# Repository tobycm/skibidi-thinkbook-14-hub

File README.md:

# skibidi thinkbook 14 hub

a very skibidi usb hub to clip on my laptop.

features:

- usb 3.2 gen 1 hub with gigabit ethernet
- 2 usb-a usb 3.2 gen 1 ports
- 2 usb-c usb 2.0 ports
- 3.5mm audio jack

powered by tusb8042a usb hub controller, rtl8153b gigabit ethernet controller, ch334 usb 2.0 hub controller, and pcm2704 usb dac.

designed in kicad 9

## PCB

## CAD

### Case

### Body

### Top

## BOM

| Item | Quantity | Total Cost | Vendor |
| :--- | :--- | :--- | :--- |
| PCB | 5 | $11.90 | JLCPCB |
| PCBA | 2 | $59.26 | JLCPCB |
| JLCPCB Shipping | 1 | $8.29 | JLCPCB |
| PJ-325C5-G | 5 | $0.90 | LCSC |
| ESD5Z5.0T1G | 20 | $0.67 | LCSC |
| BSMD1206-200-12V | 10 | $0.61 | LCSC |
| BLM21PG221SN1D | 50 | $0.83 | LCSC |
| HR911130C | 3 | $7.68 | LCSC |
| ME6211C33M5G-N | 10 | $0.47 | LCSC |
| 0603WAF4302T5E | 100 | $0.12 | LCSC |
| FRC0603F9531TS | 100 | $0.09 | LCSC |
| 0402WGF2491TCE | 200 | $0.12 | LCSC |
| HC-USB3.0-C26 | 5 | $0.53 | LCSC |
| CYA0650-4.7UH | 5 | $1.28 | LCSC |
| HC-ST-003-01-J | 20 | $2.49 | LCSC |
| TYPE-C 14PLC-H10.0 | 20 | $4.68 | LCSC |
| XL2EL89COI-111YLC-24M | 10 | $0.65 | LCSC |
| XL2EL89COI-111YLC-12M | 10 | $0.67 | LCSC |
| LCSC Shipping | 1 | $16.09 | LCSC |
| Round Hex Cap Screw kit M3 | 1 | $8.52 | Aliexpress |
| Brass Threaded Insert Nut Kit M3 | 1 | $10.54 | Aliexpress |
| **Grand Total** | **-** | **$136.39** | **-** |

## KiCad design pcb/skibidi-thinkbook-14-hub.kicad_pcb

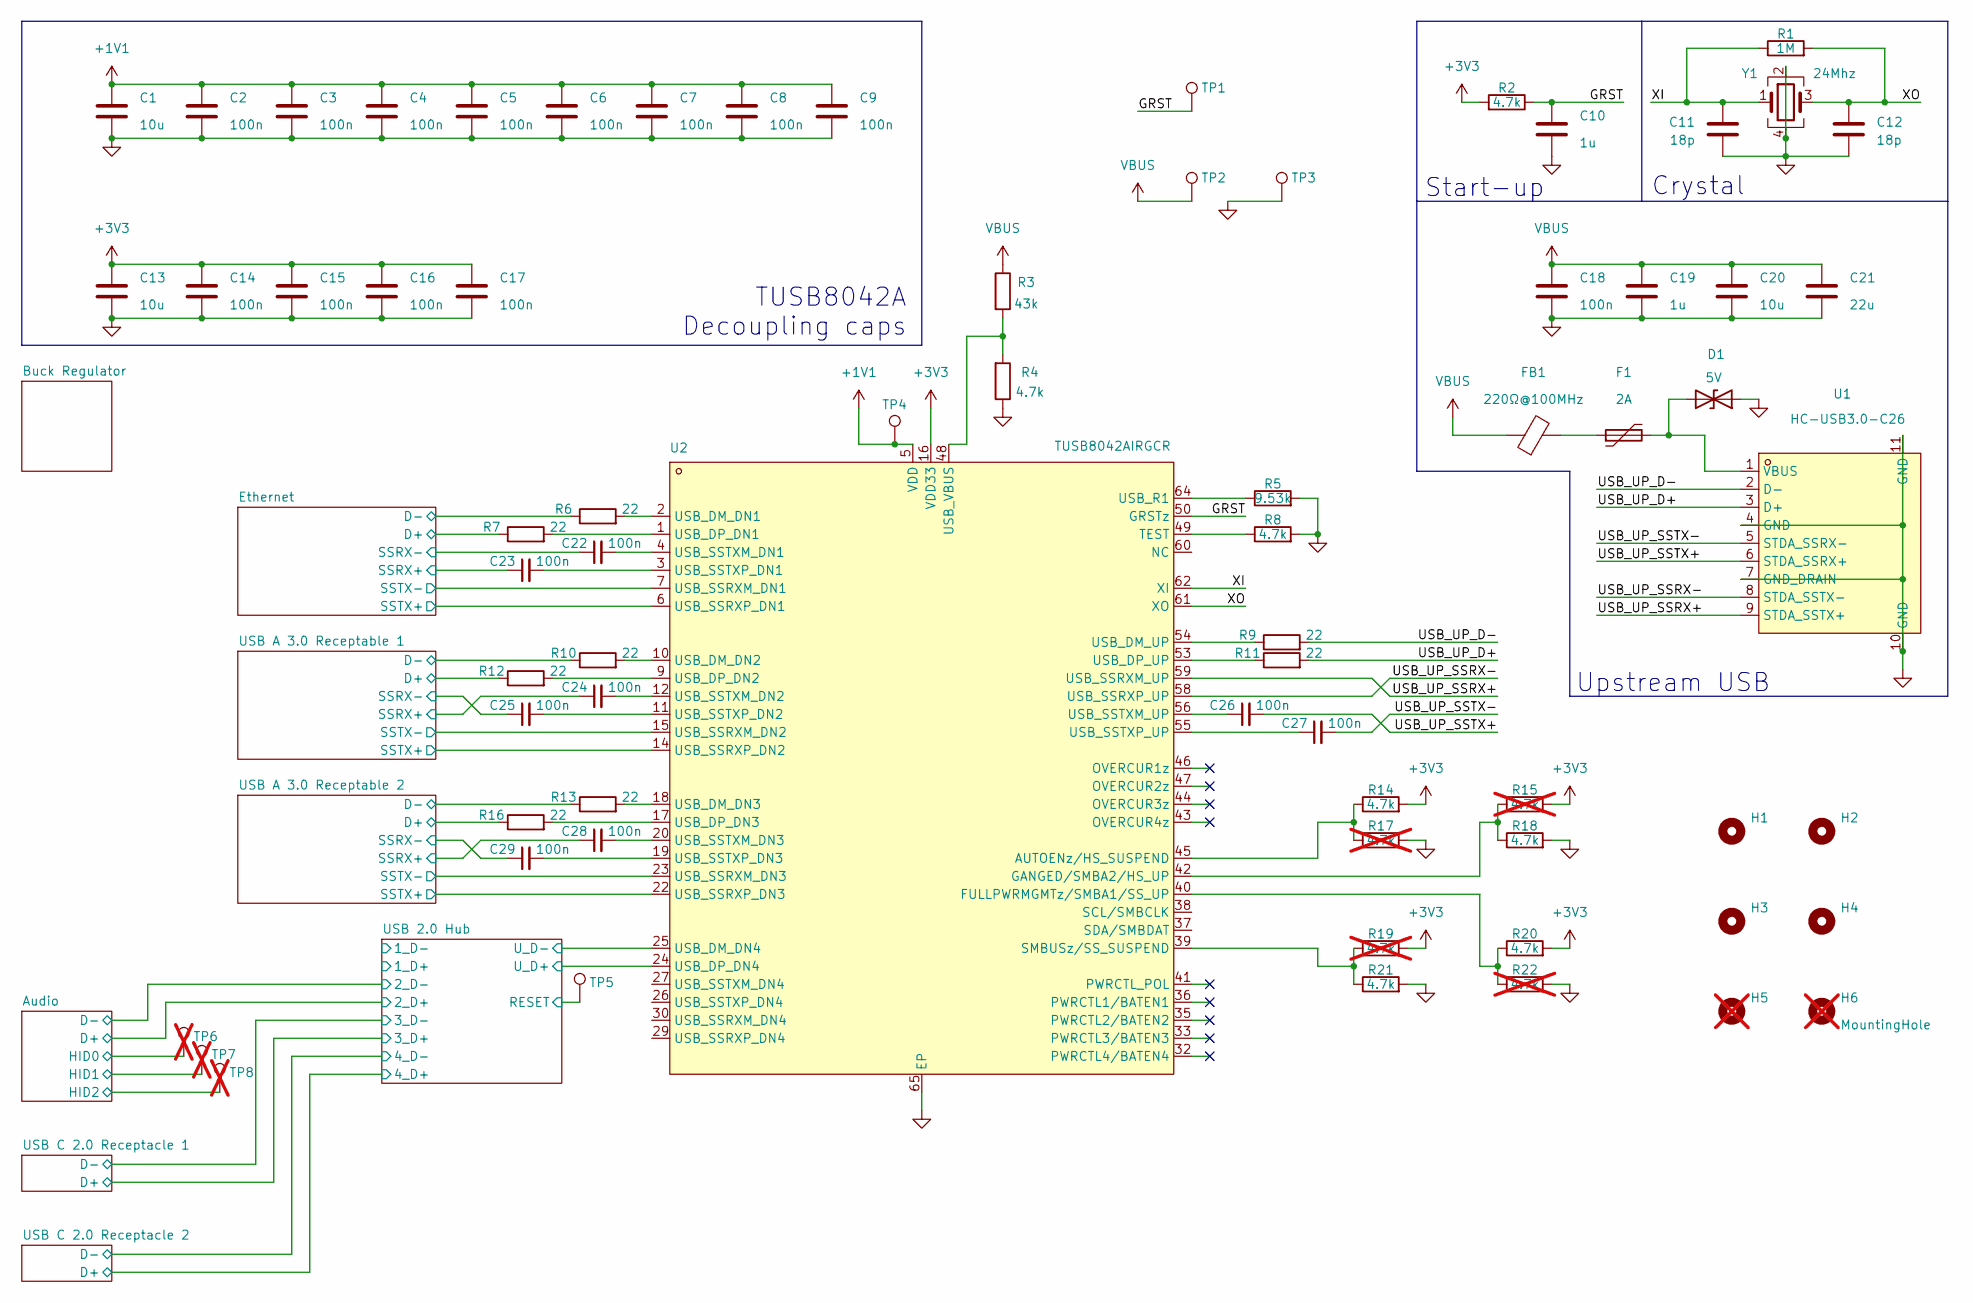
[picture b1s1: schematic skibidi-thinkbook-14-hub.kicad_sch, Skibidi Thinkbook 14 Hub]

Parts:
C1, C13, C20: 10u; C_0603_1608Metric; LCSC Part # C19702
C2, C3, C4, C5, C6, C7, C8, C9, C14, C15, C16, C17, C18, C22, C23, C24, C25, C26, C27, C28, C29: 100n; C_0402_1005Metric; LCSC Part # C307331
C10, C19: 1u; C_0603_1608Metric; LCSC Part # C15849
C11, C12: 18p; C_0402_1005Metric; LCSC Part # C1549
C21: 22u; C_0805_2012Metric; LCSC Part # C45783
D1: 5V; D_SOD-523; LCSC Part # C82044
F1: 2A; Fuse_1206_3216Metric; LCSC Part # C883135
FB1: 220Ω@100MHz; R_0805_2012Metric_Pad1.20x1.40mm_HandSolder; LCSC Part # C85840
H1, H2, H3, H4: MountingHole; MountingHole_3.2mm_M3_Pad
H5, H6: MountingHole; MountingHole_3.2mm_M3_Pad; not fitted
R1: 1M; R_0402_1005Metric; LCSC Part # C26083
R2, R4, R8, R14, R18, R20, R21: 4.7k; R_0402_1005Metric; LCSC Part # C25900
R3: 43k; R_0603_1608Metric; LCSC Part # C23172
R5: 9.53k; R_0603_1608Metric; LCSC Part # C2960722
R6, R7, R9, R10, R11, R12, R13, R16: 22; R_0402_1005Metric; LCSC Part # C25092
R15, R17, R19, R22: 4.7k; R_0402_1005Metric; LCSC Part # C25900; not fitted
TP1, TP4, TP5: TestPoint; TestPoint_Pad_D1.5mm
TP2, TP3: TestPoint; TestPoint_Pad_D2.0mm
TP6, TP7, TP8: TestPoint; TestPoint_Pad_D1.5mm; not fitted
U1: HC-USB3.0-C26; USB-3.0-A-SMD_HC-USB3.0-C26; LCSC Part C7501854
U2: TUSB8042AIRGCR; VQFN-64_L9.0-W9.0-P0.50-TL-EP6.0; LCSC Part C2860610
Y1: 24Mhz; Crystal_SMD_3225-4Pin_3.2x2.5mm; LCSC Part # C5444545

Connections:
+1V1: C1.1, C2.1, C3.1, C4.1, C5.1, C6.1, C7.1, C8.1, C9.1, TP4.1, U2.5 (VDD), U2.8 (VDD), U2.13 (VDD), U2.21 (VDD), U2.28 (VDD), U2.31 (VDD), U2.51 (VDD), U2.57 (VDD)
+3V3: C13.1, C14.1, C15.1, C16.1, C17.1, R2.2, R14.2, R15.2, R19.2, R20.2, U2.16 (VDD33), U2.34 (VDD33), U2.52 (VDD33), U2.63 (VDD33); also elsewhere on the board
/Ethernet/D+: R7.1; also elsewhere on the board
/Ethernet/D-: R6.1; also elsewhere on the board
/Ethernet/SSRX+: C23.1; also elsewhere on the board
/Ethernet/SSRX-: C22.1; also elsewhere on the board
/Ethernet/SSTX+: U2.6 (USB_SSRXP_DN1); also elsewhere on the board
/Ethernet/SSTX-: U2.7 (USB_SSRXM_DN1); also elsewhere on the board
/GRST: C10.1, R2.1, TP1.1, U2.50 (GRSTz)
/USB 2.0 Hub/RESET: TP5.1; also elsewhere on the board
/USB 2.0 Hub/U_D+: U2.24 (USB_DP_DN4); also elsewhere on the board
/USB 2.0 Hub/U_D-: U2.25 (USB_DM_DN4); also elsewhere on the board
/USB A 3.0 Receptable 1/D+: R12.1; also elsewhere on the board
/USB A 3.0 Receptable 1/D-: R10.1; also elsewhere on the board
/USB A 3.0 Receptable 1/SSRX+: C24.1; also elsewhere on the board
/USB A 3.0 Receptable 1/SSRX-: C25.1; also elsewhere on the board
/USB A 3.0 Receptable 1/SSTX+: U2.14 (USB_SSRXP_DN2); also elsewhere on the board
/USB A 3.0 Receptable 1/SSTX-: U2.15 (USB_SSRXM_DN2); also elsewhere on the board
/USB A 3.0 Receptable 2/D+: R16.1; also elsewhere on the board
/USB A 3.0 Receptable 2/D-: R13.1; also elsewhere on the board
/USB A 3.0 Receptable 2/SSRX+: C28.1; also elsewhere on the board
/USB A 3.0 Receptable 2/SSRX-: C29.1; also elsewhere on the board
/USB A 3.0 Receptable 2/SSTX+: U2.22 (USB_SSRXP_DN3); also elsewhere on the board
/USB A 3.0 Receptable 2/SSTX-: U2.23 (USB_SSRXM_DN3); also elsewhere on the board
/USB_UP_D+: R11.2, U1.3 (D+)
/USB_UP_D-: R9.2, U1.2 (D-)
/USB_UP_SSRX+: U1.9 (STDA_SSTX+), U2.59 (USB_SSRXM_UP)
/USB_UP_SSRX-: U1.8 (STDA_SSTX-), U2.58 (USB_SSRXP_UP)
/USB_UP_SSTX+: C26.2, U1.6 (STDA_SSRX+)
/USB_UP_SSTX-: C27.2, U1.5 (STDA_SSRX-)
/XI: C11.1, R1.1, U2.62 (XI), Y1.1
/XO: C12.1, R1.2, U2.61 (XO), Y1.3
GND: C1.2, C2.2, C3.2, C4.2, C5.2, C6.2, C7.2, C8.2, C9.2, C10.2, C11.2, C12.2, C13.2, C14.2, C15.2, C16.2, C17.2, C18.2, C19.2, C20.2, C21.2, D1.1 (A1), R4.1, R5.2, R8.2, R17.2, R18.2, R21.2, R22.2, TP3.1, U1.4 (GND), U1.7 (GND_DRAIN), U1.10 (GND), U1.11 (GND), U2.65 (EP), Y1.2, Y1.4; also elsewhere on the board
unnamed: D1.2 (A2), F1.2, U1.1 (VBUS)
unnamed: F1.1, FB1.2
unnamed: R14.1, R17.1, U2.45 (AUTOENz/HS_SUSPEND)
unnamed: R20.1, R22.1, U2.40 (FULLPWRMGMTz/SMBA1/SS_UP)
unnamed: R15.1, R18.1, U2.42 (GANGED/SMBA2/HS_UP)
unnamed: R19.1, R21.1, U2.39 (SMBUSz/SS_SUSPEND)
unnamed: R8.1, U2.49 (TEST)
unnamed: R6.2, U2.2 (USB_DM_DN1)
unnamed: R10.2, U2.10 (USB_DM_DN2)
unnamed: R13.2, U2.18 (USB_DM_DN3)
unnamed: R9.1, U2.54 (USB_DM_UP)
unnamed: R7.2, U2.1 (USB_DP_DN1)
unnamed: R12.2, U2.9 (USB_DP_DN2)
unnamed: R16.2, U2.17 (USB_DP_DN3)
unnamed: R11.1, U2.53 (USB_DP_UP)
unnamed: R5.1, U2.64 (USB_R1)
unnamed: C22.2, U2.4 (USB_SSTXM_DN1)
unnamed: C24.2, U2.12 (USB_SSTXM_DN2)
unnamed: C28.2, U2.20 (USB_SSTXM_DN3)
unnamed: C26.1, U2.56 (USB_SSTXM_UP)
unnamed: C23.2, U2.3 (USB_SSTXP_DN1)
unnamed: C25.2, U2.11 (USB_SSTXP_DN2)
unnamed: C29.2, U2.19 (USB_SSTXP_DN3)
unnamed: C27.1, U2.55 (USB_SSTXP_UP)
unnamed: R3.2, R4.2, U2.48 (USB_VBUS)
VBUS: C18.1, C19.1, C20.1, C21.1, FB1.1, R3.1, TP2.1; also elsewhere on the board

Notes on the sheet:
TUSB8042A Decoupling caps
Start-up
Crystal
Upstream USB

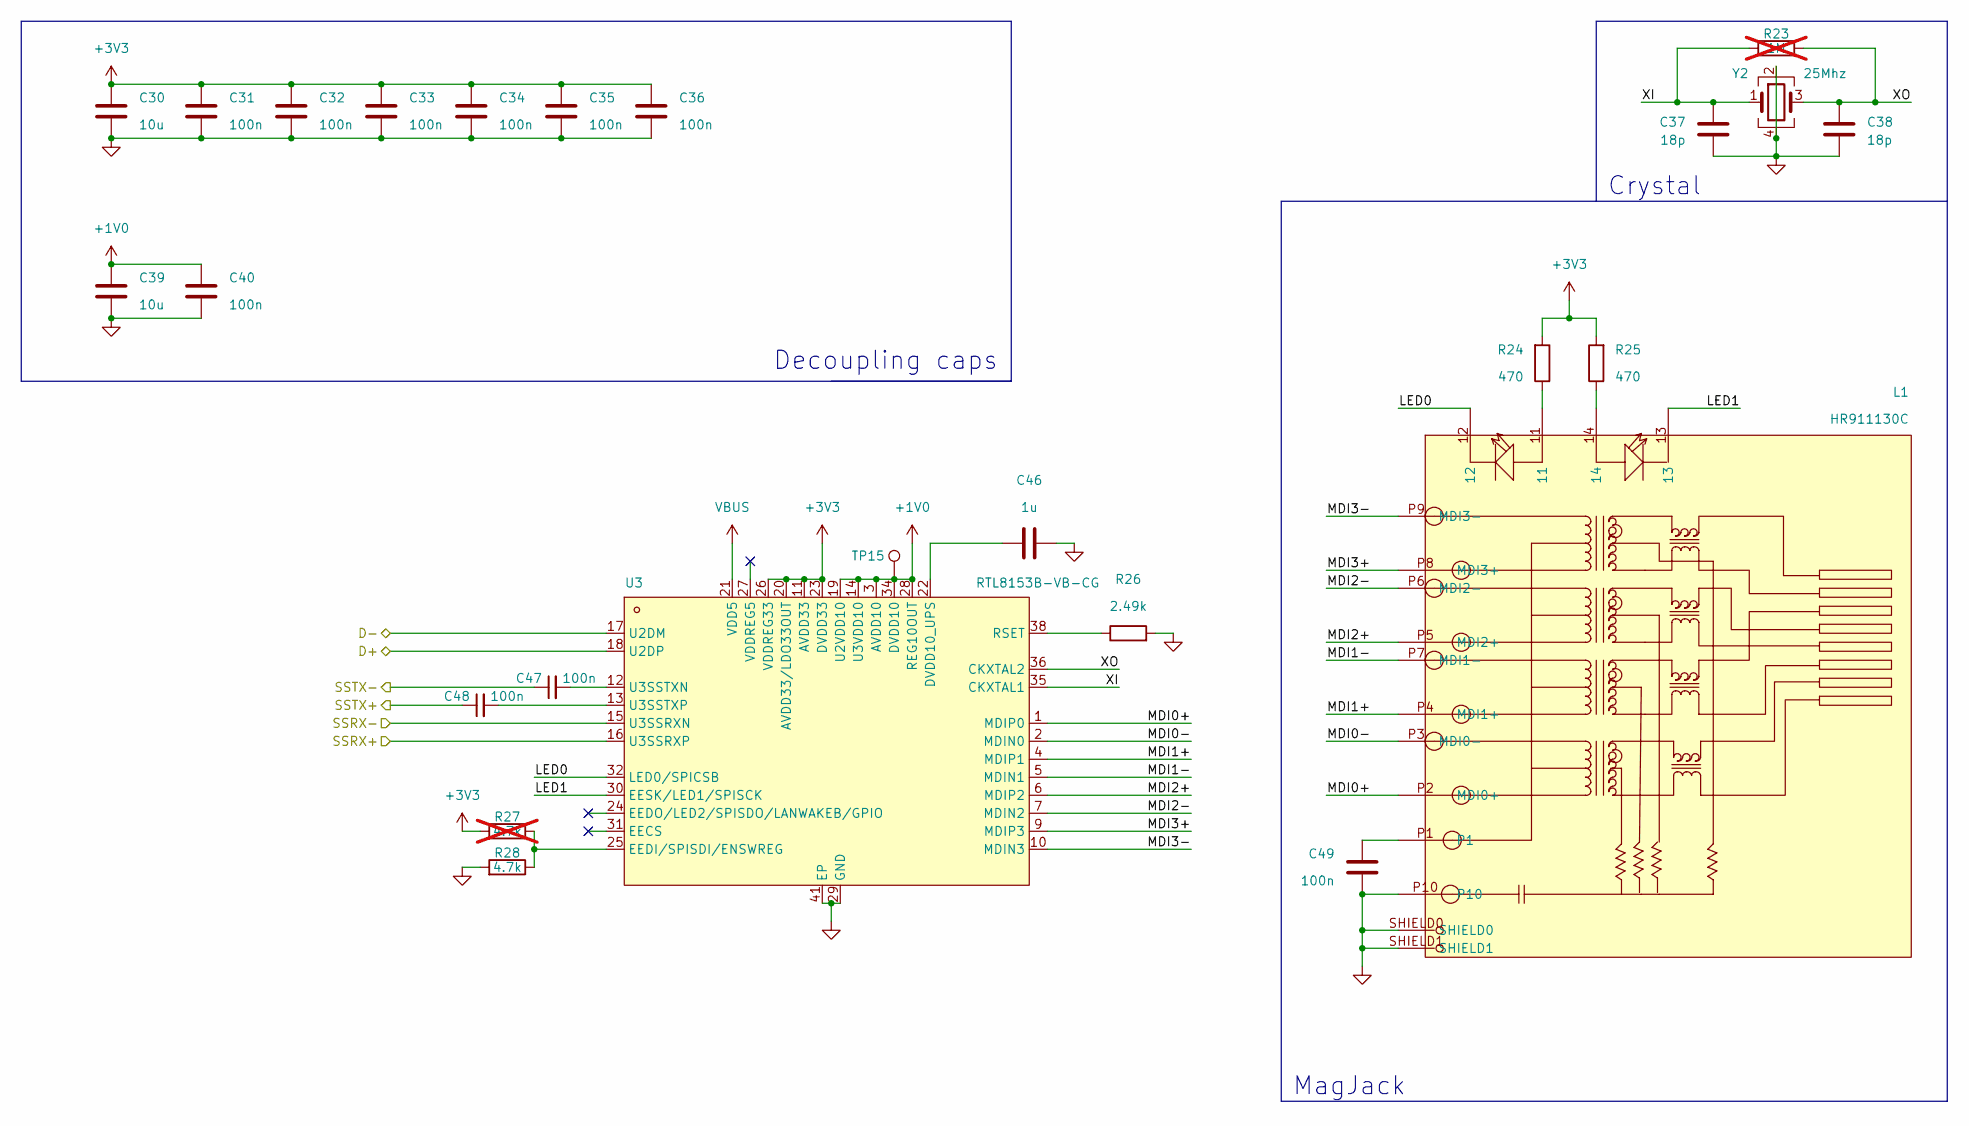
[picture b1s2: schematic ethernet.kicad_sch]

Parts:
C30, C39: 10u; C_0603_1608Metric; LCSC Part # C19702
C31, C32, C33, C34, C35, C36, C40, C47, C48, C49: 100n; C_0402_1005Metric; LCSC Part # C307331
C37, C38: 18p; C_0402_1005Metric; LCSC Part # C1549
C46: 1u; C_0603_1608Metric; LCSC Part # C15849
L1: HR911130C; RJ45-TH_HR911130C; LCSC Part C50933
R23: 1M; R_0402_1005Metric; LCSC Part # C26083; not fitted
R24, R25: 470; R_0402_1005Metric; LCSC Part # C25117
R26: 2.49k; R_0402_1005Metric; LCSC Part # C25884
R27: 4.7k; R_0402_1005Metric; LCSC Part # C25900; not fitted
R28: 4.7k; R_0402_1005Metric; LCSC Part # C25900
TP15: TestPoint; TestPoint_Pad_D1.5mm
U3: RTL8153B-VB-CG; QFN-40_L5.0-W5.0-P0.40-BL-EP3.7; LCSC Part C2802072
Y2: 25Mhz; Crystal_SMD_3225-4Pin_3.2x2.5mm; LCSC Part # C9006

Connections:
+1V0: C39.1, C40.1, TP15.1, U3.3 (AVDD10), U3.8 (AVDD10), U3.14 (U3VDD10), U3.19 (U2VDD10), U3.28 (REG10OUT), U3.34 (DVDD10), U3.37 (AVDD10)
+3V3: C30.1, C31.1, C32.1, C33.1, C34.1, C35.1, C36.1, R24.2, R25.2, R27.2, U3.11 (AVDD33), U3.20 (AVDD33/LDO33OUT), U3.23 (DVDD33), U3.26 (VDDREG33), U3.33 (DVDD33), U3.39 (AVDD33), U3.40 (AVDD33); also elsewhere on the board
/Ethernet/D+: U3.18 (U2DP); also elsewhere on the board
/Ethernet/D-: U3.17 (U2DM); also elsewhere on the board
/Ethernet/LED0: L1.12, U3.32 (LED0/SPICSB)
/Ethernet/LED1: L1.13, U3.30 (EESK/LED1/SPISCK)
/Ethernet/MDI0+: L1.P2 (MDI0+), U3.1 (MDIP0)
/Ethernet/MDI0-: L1.P3 (MDI0-), U3.2 (MDIN0)
/Ethernet/MDI1+: L1.P4 (MDI1+), U3.4 (MDIP1)
/Ethernet/MDI1-: L1.P7 (MDI1-), U3.5 (MDIN1)
/Ethernet/MDI2+: L1.P5 (MDI2+), U3.6 (MDIP2)
/Ethernet/MDI2-: L1.P6 (MDI2-), U3.7 (MDIN2)
/Ethernet/MDI3+: L1.P8 (MDI3+), U3.9 (MDIP3)
/Ethernet/MDI3-: L1.P9 (MDI3-), U3.10 (MDIN3)
/Ethernet/SSRX+: U3.16 (U3SSRXP); also elsewhere on the board
/Ethernet/SSRX-: U3.15 (U3SSRXN); also elsewhere on the board
/Ethernet/SSTX+: C48.1; also elsewhere on the board
/Ethernet/SSTX-: C47.1; also elsewhere on the board
/Ethernet/XI: C37.1, R23.1, U3.35 (CKXTAL1), Y2.1
/Ethernet/XO: C38.1, R23.2, U3.36 (CKXTAL2), Y2.3
GND: C30.2, C31.2, C32.2, C33.2, C34.2, C35.2, C36.2, C37.2, C38.2, C39.2, C40.2, C46.2, C49.2, L1.P10, L1.SHIELD0, L1.SHIELD1, R26.2, R28.2, U3.29 (GND), U3.41 (EP), Y2.2, Y2.4; also elsewhere on the board
unnamed: C49.1, L1.P1
unnamed: L1.11, R24.1
unnamed: L1.14, R25.1
unnamed: C46.1, U3.22 (DVDD10_UPS)
unnamed: R27.1, R28.1, U3.25 (EEDI/SPISDI/ENSWREG)
unnamed: R26.1, U3.38 (RSET)
unnamed: C47.2, U3.12 (U3SSTXN)
unnamed: C48.2, U3.13 (U3SSTXP)
VBUS: U3.21 (VDD5); also elsewhere on the board

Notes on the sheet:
MagJack
Decoupling caps
Crystal

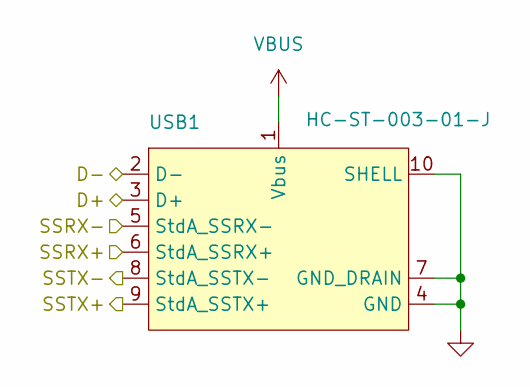
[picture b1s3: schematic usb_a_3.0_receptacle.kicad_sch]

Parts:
USB1: HC-ST-003-01-J; USB-3.0-A-TH_HC-ST-003-01-Z; LCSC Part C2845330

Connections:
/USB A 3.0 Receptable 1/D+: USB1.3 (D+); also elsewhere on the board
/USB A 3.0 Receptable 1/D-: USB1.2 (D-); also elsewhere on the board
/USB A 3.0 Receptable 1/SSRX+: USB1.6 (StdA_SSRX+); also elsewhere on the board
/USB A 3.0 Receptable 1/SSRX-: USB1.5 (StdA_SSRX-); also elsewhere on the board
/USB A 3.0 Receptable 1/SSTX+: USB1.9 (StdA_SSTX+); also elsewhere on the board
/USB A 3.0 Receptable 1/SSTX-: USB1.8 (StdA_SSTX-); also elsewhere on the board
GND: USB1.4 (GND), USB1.7 (GND_DRAIN), USB1.10 (SHELL), USB1.11 (SHELL); also elsewhere on the board
VBUS: USB1.1 (Vbus); also elsewhere on the board

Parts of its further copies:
USB2: HC-ST-003-01-J; USB-3.0-A-TH_HC-ST-003-01-Z; LCSC Part C2845330

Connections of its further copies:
/USB A 3.0 Receptable 2/D+: USB2.3 (D+); also elsewhere on the board
/USB A 3.0 Receptable 2/D-: USB2.2 (D-); also elsewhere on the board
/USB A 3.0 Receptable 2/SSRX+: USB2.6 (StdA_SSRX+); also elsewhere on the board
/USB A 3.0 Receptable 2/SSRX-: USB2.5 (StdA_SSRX-); also elsewhere on the board
/USB A 3.0 Receptable 2/SSTX+: USB2.9 (StdA_SSTX+); also elsewhere on the board
/USB A 3.0 Receptable 2/SSTX-: USB2.8 (StdA_SSTX-); also elsewhere on the board
GND: USB2.4 (GND), USB2.7 (GND_DRAIN), USB2.10 (SHELL), USB2.11 (SHELL); also elsewhere on the board
VBUS: USB2.1 (Vbus); also elsewhere on the board

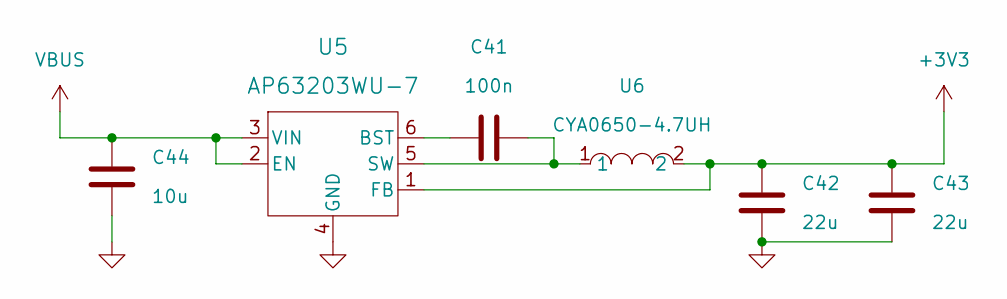
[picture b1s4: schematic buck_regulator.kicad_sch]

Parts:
C41: 100n; C_0402_1005Metric; LCSC Part # C307331
C42, C43: 22u; C_0805_2012Metric; LCSC Part # C45783
C44: 10u; C_0603_1608Metric; LCSC Part # C19702
U5: AP63203WU-7; AP63203WU-7_DIO; LCSC Part # C780769
U6: CYA0650-4.7UH; IND-SMD_L7.2-W6.6_GPSR07X0; LCSC Part C5189754

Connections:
+3V3: C42.1, C43.1, U5.1 (FB), U6.2; also elsewhere on the board
GND: C42.2, C43.2, C44.2, U5.4 (GND); also elsewhere on the board
unnamed: C41.1, U5.6 (BST)
unnamed: C41.2, U5.5 (SW), U6.1
VBUS: C44.1, U5.2 (EN), U5.3 (VIN); also elsewhere on the board

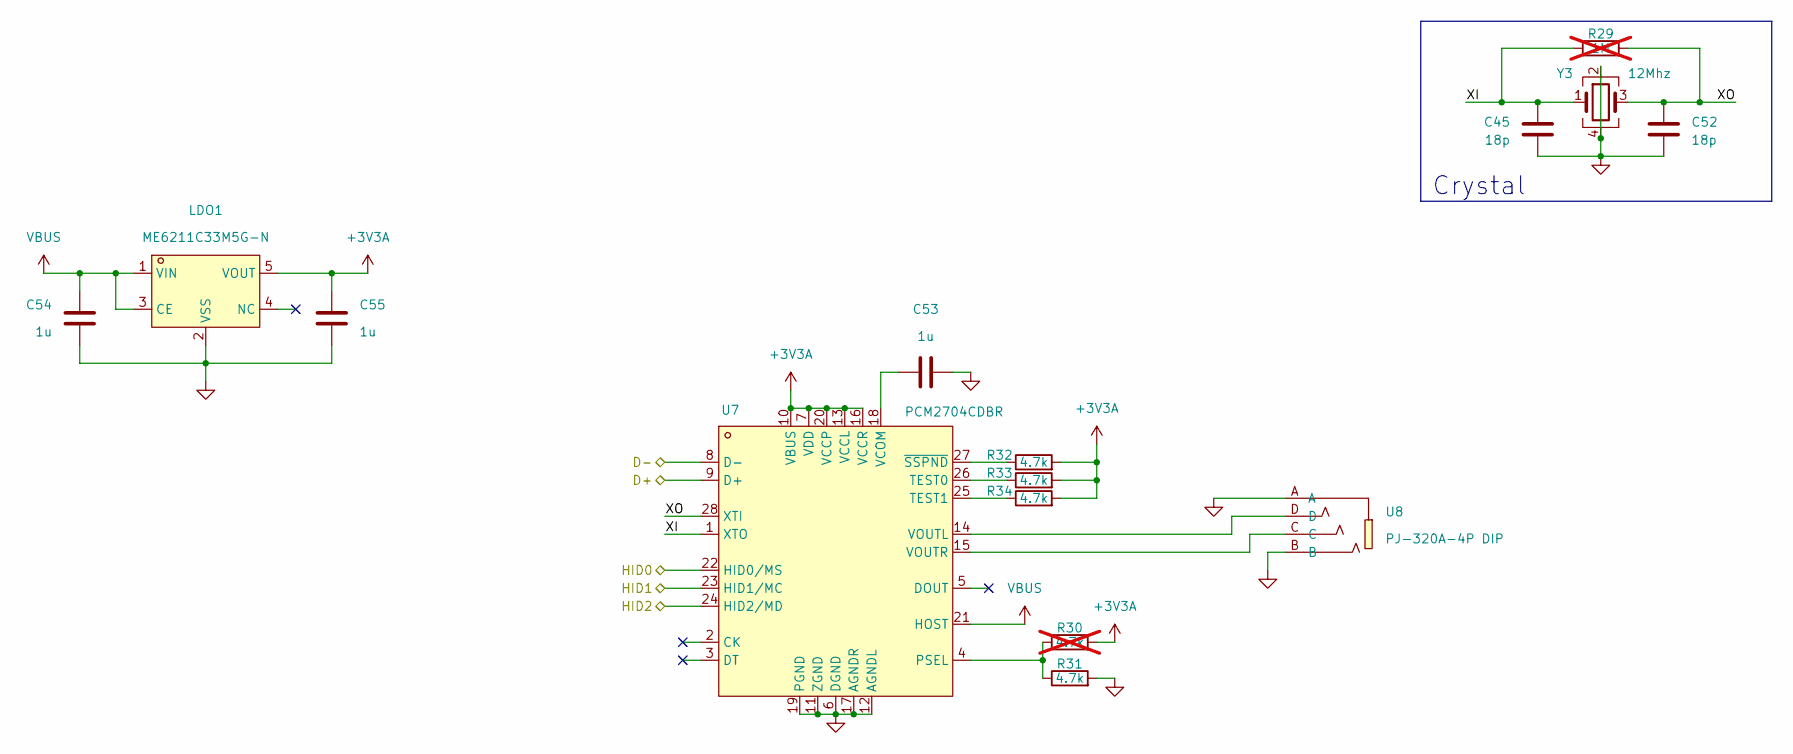
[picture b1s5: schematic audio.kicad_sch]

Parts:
C45, C52: 18p; C_0402_1005Metric; LCSC Part # C1549
C53, C54, C55: 1u; C_0603_1608Metric; LCSC Part # C15849
LDO1: ME6211C33M5G-N; SOT-23-5_L3.0-W1.7-P0.95-LS2.8-BL; LCSC Part C82942
R29: 1M; R_0402_1005Metric; LCSC Part # C26083; not fitted
R30: 4.7k; R_0402_1005Metric; LCSC Part # C25900; not fitted
R31, R32, R33, R34: 4.7k; R_0402_1005Metric; LCSC Part # C25900
U7: PCM2704CDBR; SSOP-28_L10.2-W5.3-P0.65-LS7.8-BL; LCSC Part C2859784
U8: PJ-320A-4P DIP; AUDIO-TH_PJ-320A-4P-DIP; LCSC Part C18185602
Y3: 12Mhz; Crystal_SMD_3225-4Pin_3.2x2.5mm; LCSC Part # C5280578

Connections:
+3V3A: C55.1, LDO1.5 (VOUT), R30.2, R32.2, R33.2, R34.2, U7.7 (VDD), U7.10 (VBUS), U7.13 (VCCL), U7.16 (VCCR), U7.20 (VCCP)
/Audio/D+: U7.9 (D+); also elsewhere on the board
/Audio/D-: U7.8 (D-); also elsewhere on the board
/Audio/HID0: U7.22 (HID0/MS)
/Audio/HID1: U7.23 (HID1/MC)
/Audio/HID2: U7.24 (HID2/MD)
/Audio/XI: C45.1, R29.1, U7.1 (XTO), Y3.1
/Audio/XO: C52.1, R29.2, U7.28 (XTI), Y3.3
GND: C45.2, C52.2, C53.2, C54.2, C55.2, LDO1.2 (VSS), R31.2, U7.6 (DGND), U7.11 (ZGND), U7.12 (AGNDL), U7.17 (AGNDR), U7.19 (PGND), U8.A, U8.B, Y3.2, Y3.4; also elsewhere on the board
unnamed: R30.1, R31.1, U7.4 (PSEL)
unnamed: R33.1, U7.26 (TEST0)
unnamed: R34.1, U7.25 (TEST1)
unnamed: C53.1, U7.18 (VCOM)
unnamed: U7.14 (VOUTL), U8.D
unnamed: U7.15 (VOUTR), U8.C
unnamed: R32.1, U7.27 (~SSPND)
VBUS: C54.1, LDO1.1 (VIN), LDO1.3 (CE), U7.21 (HOST); also elsewhere on the board

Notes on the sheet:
Crystal

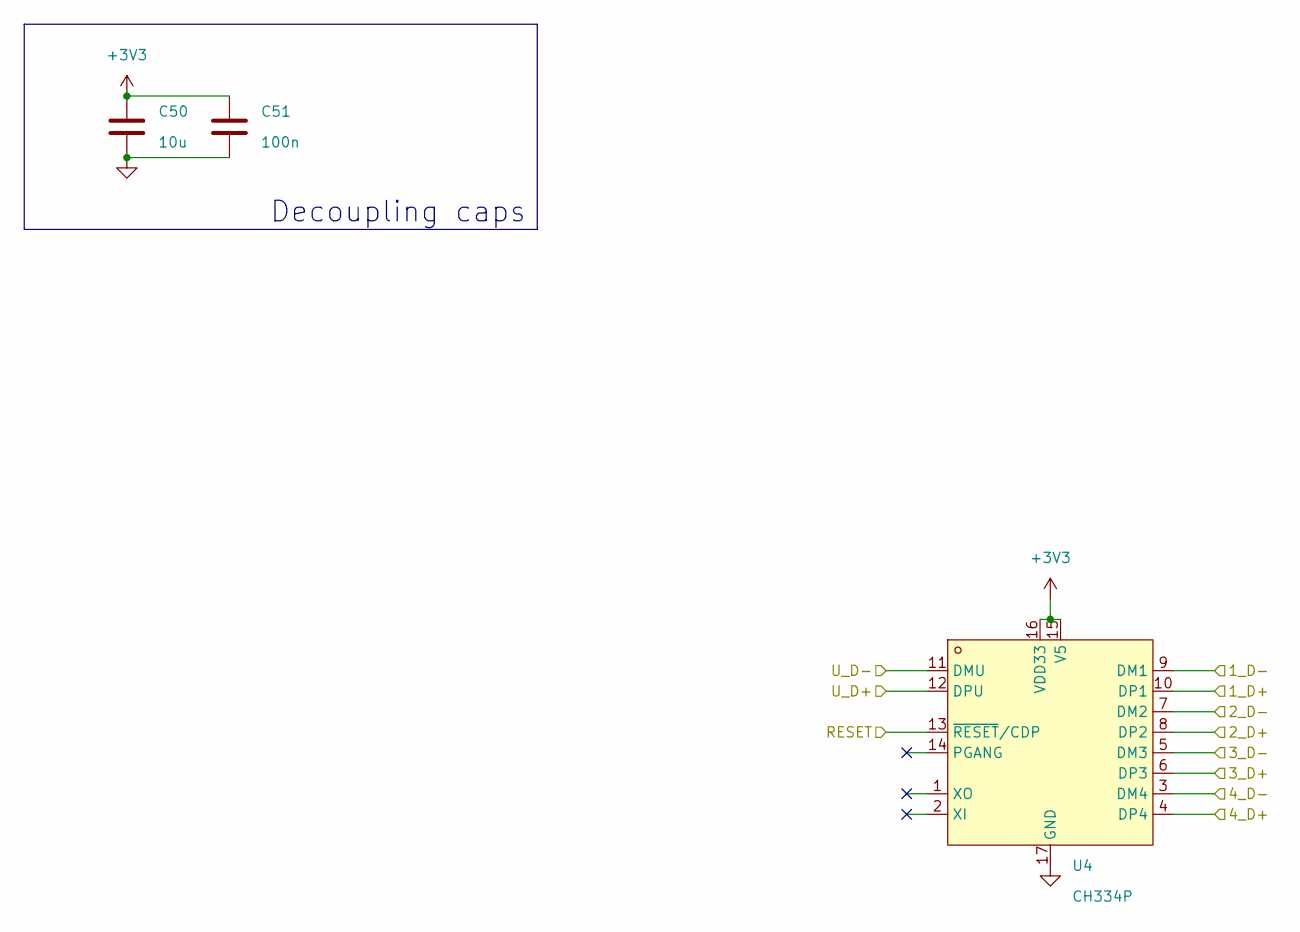
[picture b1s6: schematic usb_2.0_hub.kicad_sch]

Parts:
C50: 10u; C_0603_1608Metric; LCSC Part # C19702
C51: 100n; C_0402_1005Metric; LCSC Part # C307331
U4: CH334P; QFN-16_L3.0-W3.0-P0.50-BL-EP1.7; LCSC Part C5373042

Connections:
+3V3: C50.1, C51.1, U4.15 (V5), U4.16 (VDD33); also elsewhere on the board
/Audio/D+: U4.8 (DP2); also elsewhere on the board
/Audio/D-: U4.7 (DM2); also elsewhere on the board
/USB 2.0 Hub/1_D+: U4.10 (DP1)
/USB 2.0 Hub/1_D-: U4.9 (DM1)
/USB 2.0 Hub/3_D+: U4.6 (DP3); also elsewhere on the board
/USB 2.0 Hub/3_D-: U4.5 (DM3); also elsewhere on the board
/USB 2.0 Hub/4_D+: U4.4 (DP4); also elsewhere on the board
/USB 2.0 Hub/4_D-: U4.3 (DM4); also elsewhere on the board
/USB 2.0 Hub/RESET: U4.13 (~RESET/CDP); also elsewhere on the board
/USB 2.0 Hub/U_D+: U4.12 (DPU); also elsewhere on the board
/USB 2.0 Hub/U_D-: U4.11 (DMU); also elsewhere on the board
GND: C50.2, C51.2, U4.17 (GND); also elsewhere on the board

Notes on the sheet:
Decoupling caps

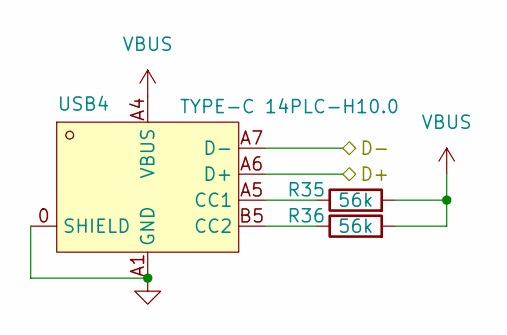
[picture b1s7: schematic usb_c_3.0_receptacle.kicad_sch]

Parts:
R35, R36: 56k; R_0402_1005Metric; LCSC Part # C25796
USB4: TYPE-C 14PLC-H10.0; USB-C-TH_SHOUHAN_TYPE-C-14PLC-H10.0; LCSC Part C3151746

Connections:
/USB 2.0 Hub/3_D+: USB4.A6 (D+), USB4.B6 (D+); also elsewhere on the board
/USB 2.0 Hub/3_D-: USB4.A7 (D-), USB4.B7 (D-); also elsewhere on the board
GND: USB4.0 (SHIELD), USB4.A1 (GND), USB4.A12 (GND), USB4.B1 (GND), USB4.B12 (GND); also elsewhere on the board
unnamed: R35.1, USB4.A5 (CC1)
unnamed: R36.1, USB4.B5 (CC2)
VBUS: R35.2, R36.2, USB4.A4 (VBUS), USB4.A9 (VBUS), USB4.B4 (VBUS), USB4.B9 (VBUS); also elsewhere on the board

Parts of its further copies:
R37, R38: 56k; R_0402_1005Metric; LCSC Part # C25796
USB5: TYPE-C 14PLC-H10.0; USB-C-TH_SHOUHAN_TYPE-C-14PLC-H10.0; LCSC Part C3151746

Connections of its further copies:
/USB 2.0 Hub/4_D+: USB5.A6 (D+), USB5.B6 (D+); also elsewhere on the board
/USB 2.0 Hub/4_D-: USB5.A7 (D-), USB5.B7 (D-); also elsewhere on the board
GND: USB5.0 (SHIELD), USB5.A1 (GND), USB5.A12 (GND), USB5.B1 (GND), USB5.B12 (GND); also elsewhere on the board
unnamed: R37.1, USB5.A5 (CC1)
unnamed: R38.1, USB5.B5 (CC2)
VBUS: R37.2, R38.2, USB5.A4 (VBUS), USB5.A9 (VBUS), USB5.B4 (VBUS), USB5.B9 (VBUS); also elsewhere on the board

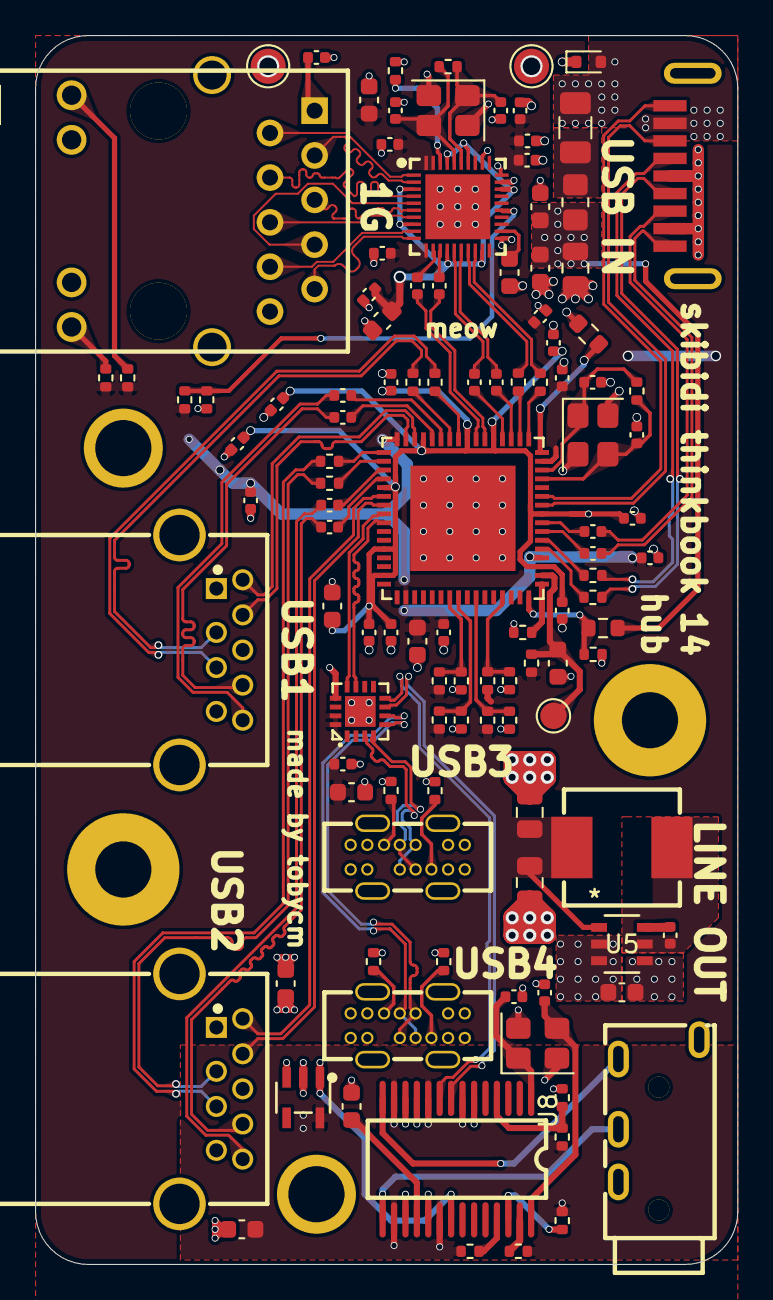
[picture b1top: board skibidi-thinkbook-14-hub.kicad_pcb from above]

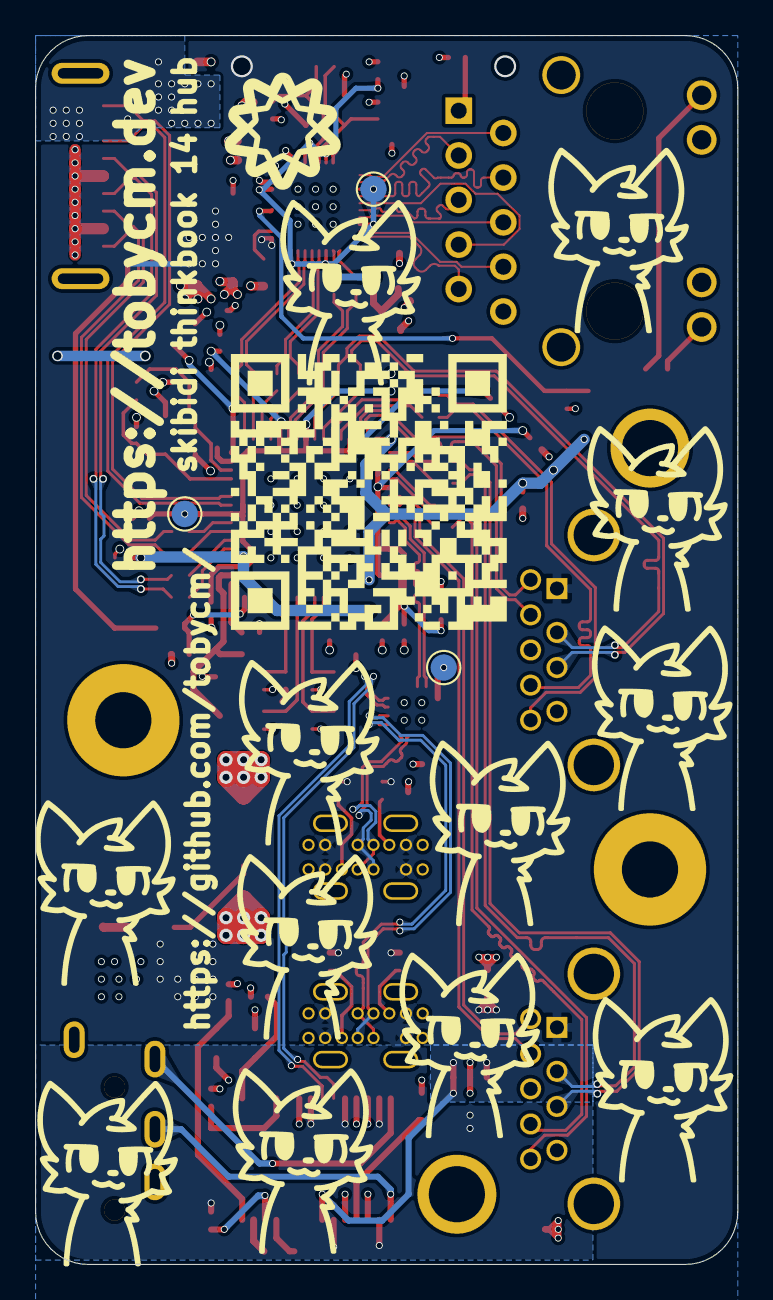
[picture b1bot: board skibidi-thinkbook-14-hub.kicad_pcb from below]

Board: 4 copper layers, 40.0 x 70.0 mm, 121 parts (3 on the bottom side), 102 nets.

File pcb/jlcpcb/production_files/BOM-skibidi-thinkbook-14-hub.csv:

Comment,Designator,Footprint,LCSC,Quantity
100n,"C14,C15,C16,C17,C2,C22,C23,C24,C25,C26,C27,C28,C29,C3,C31,C32,C33,C34,C35,C36,C4,C40,C41,C47,C48,C49,C5,C51,C6,C7,C8,C9",C_0402_1005Metric,C307331,32
10u,"C1,C13,C20,C30,C39,C44,C50",C_0603_1608Metric,C19702,7
18p,"C11,C12,C37,C38,C45,C52",C_0402_1005Metric,C1549,6
1M,R1,R_0402_1005Metric,C26083,1
1u,"C10,C19,C46,C53,C54,C55",C_0603_1608Metric,C15849,6
22,"R10,R11,R12,R13,R16,R6,R7,R9",R_0402_1005Metric,C25092,8
22u,"C21,C42,C43",C_0805_2012Metric,C45783,3
25Mhz,Y2,Crystal_SMD_3225-4Pin_3.2x2.5mm,C9006,1
4.7k,"R14,R17,R18,R2,R20,R21,R27,R28,R31,R32,R33,R34,R4,R8",R_0402_1005Metric,C25900,14
470,"R24,R25",R_0402_1005Metric,C25117,2
56k,"R35,R36,R37,R38",R_0402_1005Metric,C25796,4
AP63203WU-7,U5,AP63203WU-7_DIO,C780769,1
CH334P,U4,QFN-16_L3.0-W3.0-P0.50-BL-EP1.7,C5373042,1
PCM2704CDBR,U7,SSOP-28_L10.2-W5.3-P0.65-LS7.8-BL,C2859784,1
RTL8153B-VB-CG,U3,QFN-40_L5.0-W5.0-P0.40-BL-EP3.7,C2802072,1
TUSB8042AIRGCR,U2,VQFN-64_L9.0-W9.0-P0.50-TL-EP6.0,C2860610,1

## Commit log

2025-12-30 pcb done!
2025-12-31 add cad and readme. update pcb a bit too
2026-01-01 added bom to readme, completed project
2026-01-07 gitignored my bom :c
    add gerber zip
2026-04-25 add gerbers
